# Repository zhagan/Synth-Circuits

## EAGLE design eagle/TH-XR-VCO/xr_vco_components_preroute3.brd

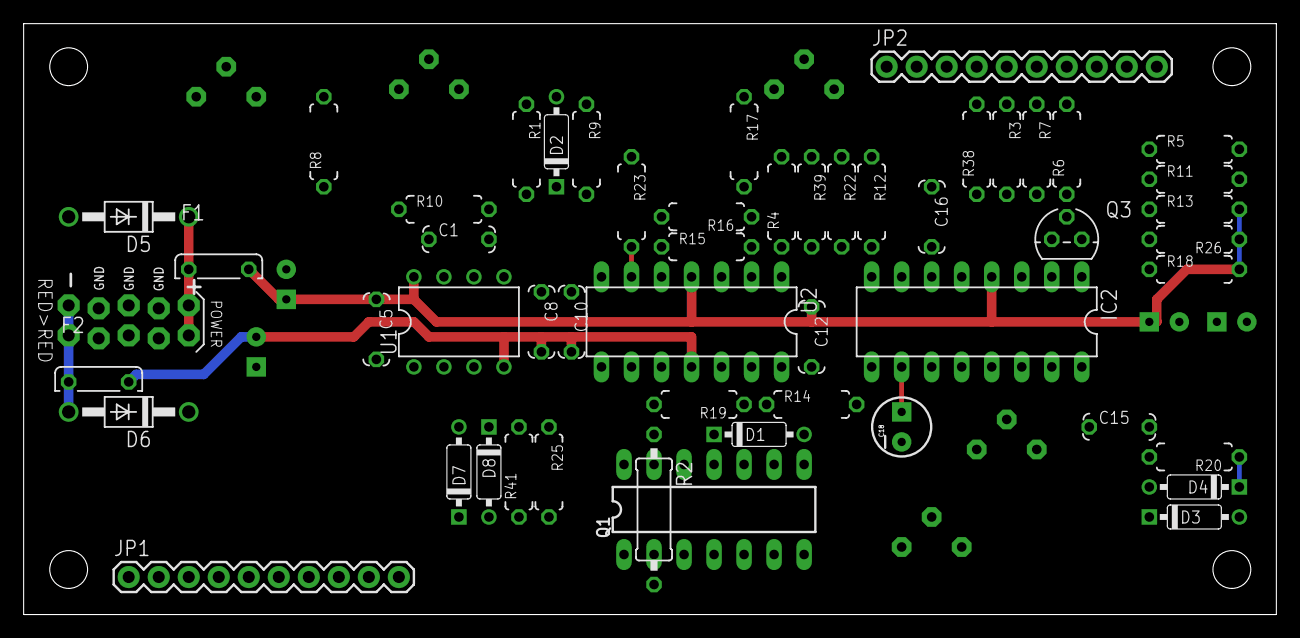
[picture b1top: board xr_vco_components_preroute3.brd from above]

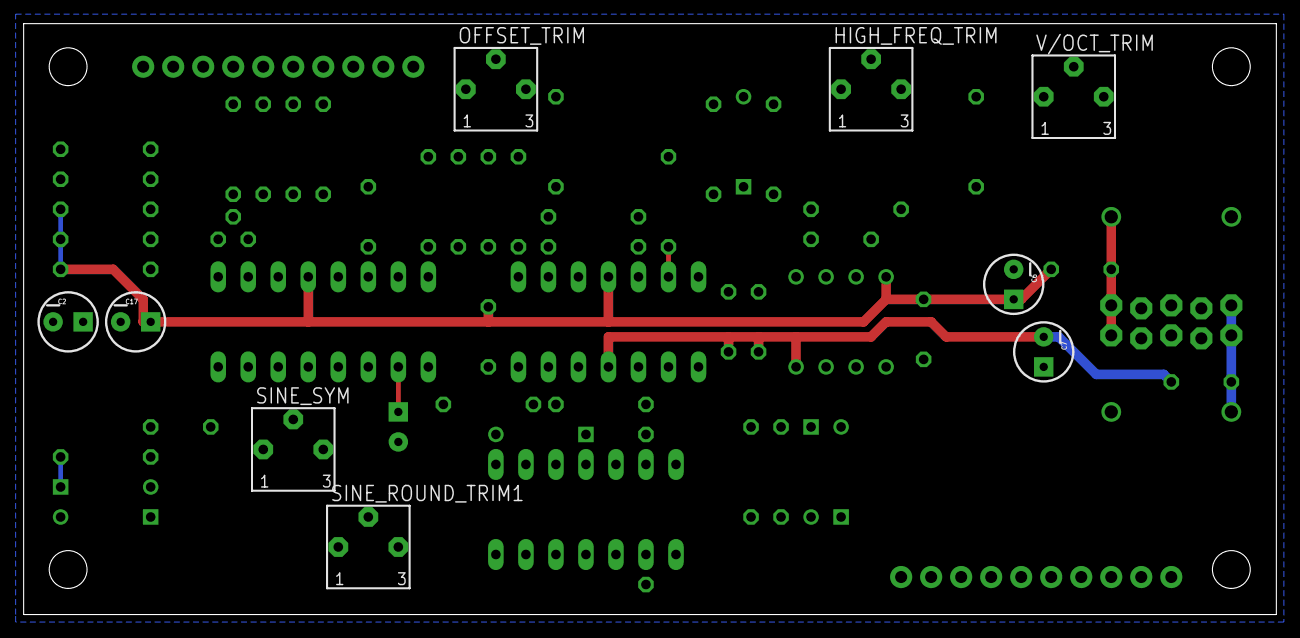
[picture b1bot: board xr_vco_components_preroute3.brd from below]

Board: 2 copper layers, 106.0 x 50.0 mm, 66 parts (9 on the bottom side), 48 nets.

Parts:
C1: 100pf; C050-024X044
C2, C6, C7: 10uf; CPOL-RADIAL-10UF-25V
C5, C8, C10, C12: 100n; C050-024X044
C15: 470pf; C050-024X044
C16: 0.047uf; C050-024X044
C17, C18: 4.7uf; CPOL-RADIAL-10UF-25V
D1, D2, D3, D4, D7, D8: 1N4148; DO35-7
D5, D6: 1N4001; DO41-10
F1, F2: FUSE; C050H075X075
HIGH_FREQ_TRIM: 1M; BOURNS_3362P_TRIMMER
IC2: DIL16
JP1, JP2: M10"; 1X10
OFFSET_TRIM: 50k; BOURNS_3362P_TRIMMER
Q1: THAT300P; DIL14
Q3: 2N3904; TO92D
R1: 47k; 7MM_RESISTOR
R2: 2k; 0309/12
R3: 82k; 7MM_RESISTOR
R4, R12: 1k; 7MM_RESISTOR
R5: 11k; 7MM_RESISTOR
R6: 20k; 7MM_RESISTOR
R7, R11: 5.6k; 7MM_RESISTOR
R8: 390R; 7MM_RESISTOR
R9, R13, R26: 4.7k; 7MM_RESISTOR
R10: 1.2m; 7MM_RESISTOR
R14, R18, R19, R23, R25: 10k; 7MM_RESISTOR
R15: 2.2M; 7MM_RESISTOR
R16: 3k; 7MM_RESISTOR
R17: 1.8k; 7MM_RESISTOR
R20: 100k; 7MM_RESISTOR
R22: 2.2k; 7MM_RESISTOR
R38: 150k; 7MM_RESISTOR
R39: 200k; 7MM_RESISTOR
R41: 220k; 7MM_RESISTOR
SINE_ROUND_TRIM1: 500 Ohm; BOURNS_3362P_TRIMMER
SINE_SYM: 25k; BOURNS_3362P_TRIMMER
SV1: EURO_POWER_HEADERLOCK_PADS; EURO_PWR_HEADER_LOCK
U1: LF442N; DIL08
U2: TL074P; DIL14
U$1, U$2, U$3, U$4: MOUNTING_HOLE
V/OCT_TRIM: 100R; BOURNS_3362P_TRIMMER

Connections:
+12V: C5.1, C6.1, C12.1, C17.1, F1.2, IC2.4, JP1.10, R7.2, R13.2, R18.2, R26.1, U1.8, U2.4
+12V_INLET: D5.C, F1.1, SV1.POS1, SV1.POS2
-12V: C7.2, C8.2, C10.2, F2.2, JP1.8, R10.1, R38.1, U1.4, U2.11
-12V_INLET: D6.A, F2.1, SV1.NEG1, SV1.NEG2
CATH_D4: D1.C, R19.1, U2.14
GND: C2.2, C5.2, C6.2, C7.1, C8.1, C10.1, C12.2, C17.2, C18.2, D3.A, D4.A, D5.A, D6.C, IC2.12, JP1.9, Q1.13, Q3.E, R8.1, R11.1, R12.1, R17.1, R23.1, SINE_SYM.2, SV1.GND1, SV1.GND2, SV1.GND3, SV1.GND4, SV1.GND5, SV1.GND6, U1.3, U1.5, U2.3, U2.10, U2.12
LIN_FM_CV: C1.2, JP1.4, Q1.3, R10.2, U1.6
unnamed: IC2.7, Q1.12
unnamed: D2.C, R1.2
unnamed: HIGH_FREQ_TRIM.1, R1.1
unnamed: IC2.2, R3.2
unnamed: R2.2, U1.1, V/OCT_TRIM.3
unnamed: OFFSET_TRIM.3, R3.1, R39.1, U2.2
unnamed: R8.2, V/OCT_TRIM.1
unnamed: D2.A, Q1.2, V/OCT_TRIM.2
unnamed: Q1.1, Q1.14, R9.2
unnamed: OFFSET_TRIM.1, R38.2
unnamed: R4.1, R39.2, U2.1
unnamed: C1.1, HIGH_FREQ_TRIM.3, R9.1, U1.7
unnamed: C2.1, R5.2, R6.2, R7.1, R11.2
unnamed: IC2.16, SINE_SYM.1
unnamed: IC2.13, SINE_ROUND_TRIM1.1
unnamed: IC2.15, SINE_SYM.3
unnamed: IC2.8, R12.2
unnamed: R18.1, R23.2, U2.6
unnamed: R15.1, R16.2, U2.7
unnamed: R19.2, R25.1, U2.13
unnamed: R15.2, R22.1, U2.5
unnamed: D1.A, D3.C, IC2.1, R14.1
unnamed: C15.2, R20.2
unnamed: D4.C, Q3.B, R20.1
unnamed: IC2.11, R13.1, R14.2, R22.2
unnamed: IC2.9, Q3.C, R26.2
unnamed: C16.2, IC2.6
unnamed: C16.1, IC2.5
unnamed: C18.1, IC2.10
unnamed: D7.A, D8.C, U2.8
unnamed: D8.A, R25.2, R41.1
PITCH_CV: JP1.7, R2.1, U1.2
SINE_TRI_OUT: JP1.3, R4.2
SKEW_IN: D7.C, JP1.5, R41.2, U2.9
SQR_OUT: JP1.2, R16.1, R17.2
SW_1: JP2.10, R6.1
SW_2: IC2.3, JP2.9
SW_3: JP2.8, R5.1
SW_4: JP2.7, SINE_ROUND_TRIM1.3
SW_5: IC2.14, JP2.6
SYNC_IN: C15.1, JP1.6

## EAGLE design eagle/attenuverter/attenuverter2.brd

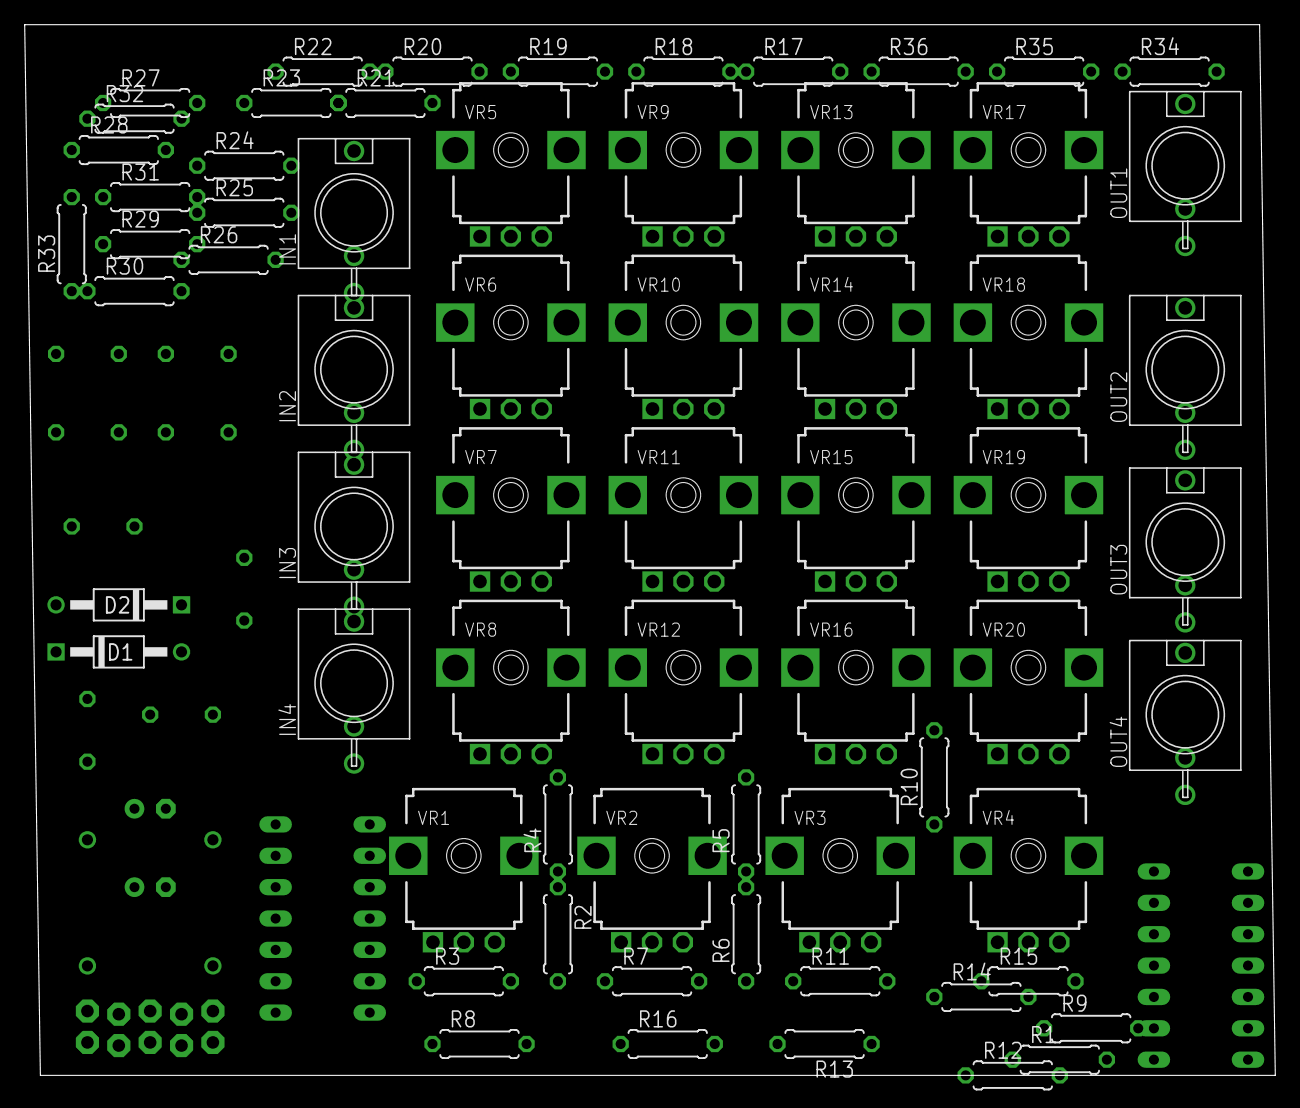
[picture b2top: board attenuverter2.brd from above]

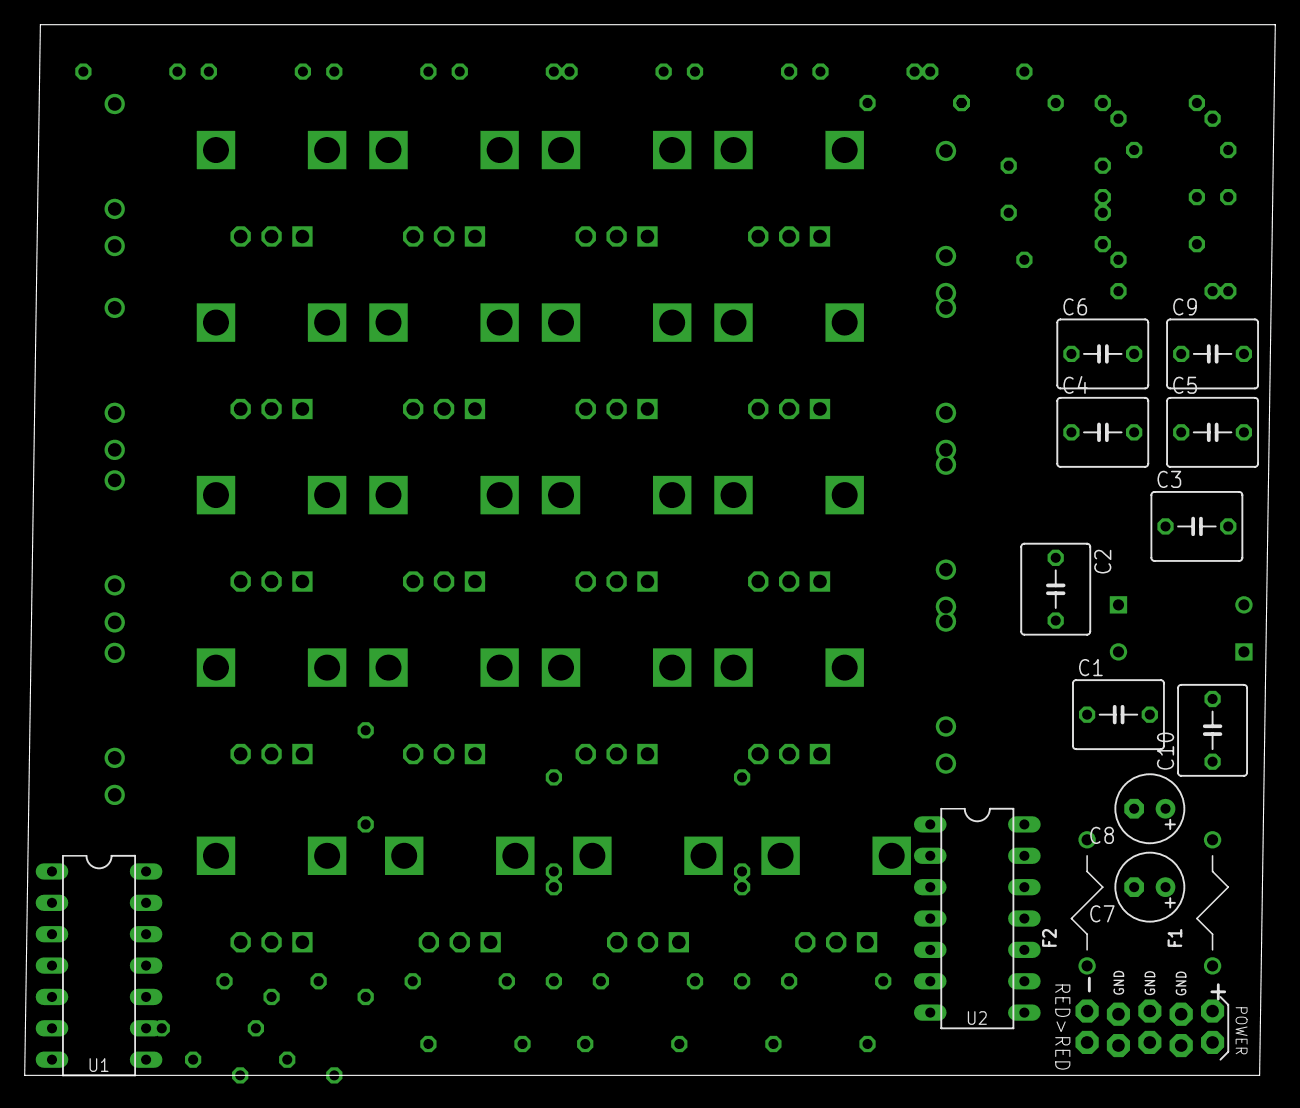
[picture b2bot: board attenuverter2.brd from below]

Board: 2 copper layers, 101.3 x 85.1 mm, 81 parts (15 on the bottom side), 49 nets, no tracks yet.

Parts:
C1, C2, C3, C4, C5, C6, C9, C10: 100nF; C050-055X075
C7, C8: 10uF; E2,5-6
D1, D2: 1N4007; DO41-4
F1, F2: MF-R500+; BOURNS-MF-R
IN1, IN2, IN3, IN4: THONKICONNNEW; WQP-PJ301M-12_JACK
OUT1, OUT2, OUT3, OUT4: THONKICONNNEW; WQP-PJ301M-12_JACK
R1, R2, R4, R5, R6, R8, R9, R10, R12, R13, R14, R16, R17, R18, R19, R20, R21, R22, R23, R24, R25, R26, R27, R28, R29, R30, R31, R32, R33, R34, R35, R36: 10k; 0207/7
R3, R7, R11, R15: 4.7k; 0207/7
SV1: EURO_POWER_HEADERLOCK_PADS; EURO_PWR_HEADER_LOCK
U1, U2: TL074_; DIL14
VR1, VR2, VR3, VR4, VR5, VR6, VR7, VR8, VR9, VR10, VR11, VR12, VR13, VR14, VR15, VR16, VR17, VR18, VR19, VR20: B10k; 9MM_SNAP-IN_POT

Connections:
+12V: C1.1, C3.1, C5.1, C7.+, C9.1, D1.C, F1.P$2, U1.4, U2.4
-12V: C2.2, C4.2, C6.2, C8.-, C10.2, D2.A, F2.P$1, U1.11, U2.11
GND: C1.2, C2.1, C3.2, C4.1, C5.2, C6.1, C7.-, C8.+, C9.2, C10.1, D1.A, D2.C, IN1.P$3_SLEEVE, IN2.P$3_SLEEVE, IN3.P$3_SLEEVE, IN4.P$3_SLEEVE, OUT1.P$3_SLEEVE, OUT2.P$3_SLEEVE, OUT3.P$3_SLEEVE, OUT4.P$3_SLEEVE, SV1.GND1, SV1.GND2, SV1.GND3, SV1.GND4, SV1.GND5, SV1.GND6, U2.3, U2.6, U2.9, U2.13, VR1.2, VR2.2, VR3.2, VR4.2, VR5.1, VR6.1, VR7.1, VR8.1, VR9.1, VR10.1, VR11.1, VR12.1, VR13.1, VR14.1, VR15.1, VR16.1, VR17.1, VR18.1, VR19.1, VR20.1
unnamed: R1.1, R2.2, R3.2, U1.3
unnamed: R2.1, R4.1, R19.2, U2.1
unnamed: R4.2, U1.2, VR1.3
unnamed: R3.1, VR1.1
unnamed: R22.2, R23.1, R24.2, R25.2, R26.2, U2.5
unnamed: R5.1, R6.2, R7.2, U1.5
unnamed: OUT1.P$1_TIP, R1.2, U1.1
unnamed: R8.2, U1.6, VR2.3
unnamed: F1.P$1, SV1.POS1, SV1.POS2
unnamed: F2.P$2, SV1.NEG1, SV1.NEG2
unnamed: R7.1, VR2.1
unnamed: OUT2.P$1_TIP, R5.2, U1.7
unnamed: R22.1, VR9.2
unnamed: R9.1, R10.2, R11.2, U1.10
unnamed: R12.2, U1.9, VR3.3
unnamed: R11.1, VR3.1
unnamed: OUT3.P$1_TIP, R9.2, U1.8
unnamed: IN4.P$1_TIP, VR8.3, VR12.3, VR16.3, VR20.3
unnamed: R13.1, R14.2, R15.2, U1.12
unnamed: R16.2, U1.13, VR4.3
unnamed: R15.1, VR4.1
unnamed: OUT4.P$1_TIP, R13.2, U1.14
unnamed: IN2.P$1_TIP, VR6.3, VR10.3, VR14.3, VR18.3
unnamed: R17.2, R18.2, R19.1, R20.2, R21.2, U2.2
unnamed: R18.1, VR5.2
unnamed: R17.1, VR6.2
unnamed: IN3.P$1_TIP, VR7.3, VR11.3, VR15.3, VR19.3
unnamed: R20.1, VR7.2
unnamed: R21.1, VR8.2
unnamed: R24.1, VR10.2
unnamed: R25.1, VR11.2
unnamed: R26.1, VR12.2
unnamed: IN1.P$1_TIP, VR5.3, VR9.3, VR13.3, VR17.3
unnamed: R6.1, R8.1, R23.2, U2.7
unnamed: R27.2, R28.1, R29.2, R30.2, R31.2, U2.10
unnamed: R27.1, VR13.2
unnamed: R29.1, VR14.2
unnamed: R30.1, VR15.2
unnamed: R31.1, VR16.2
unnamed: R10.1, R12.1, R28.2, U2.8
unnamed: R32.2, R33.1, R34.2, R35.2, R36.2, U2.12
unnamed: R32.1, VR17.2
unnamed: R34.1, VR18.2
unnamed: R35.1, VR19.2
unnamed: R36.1, VR20.2
unnamed: R14.1, R16.1, R33.2, U2.14

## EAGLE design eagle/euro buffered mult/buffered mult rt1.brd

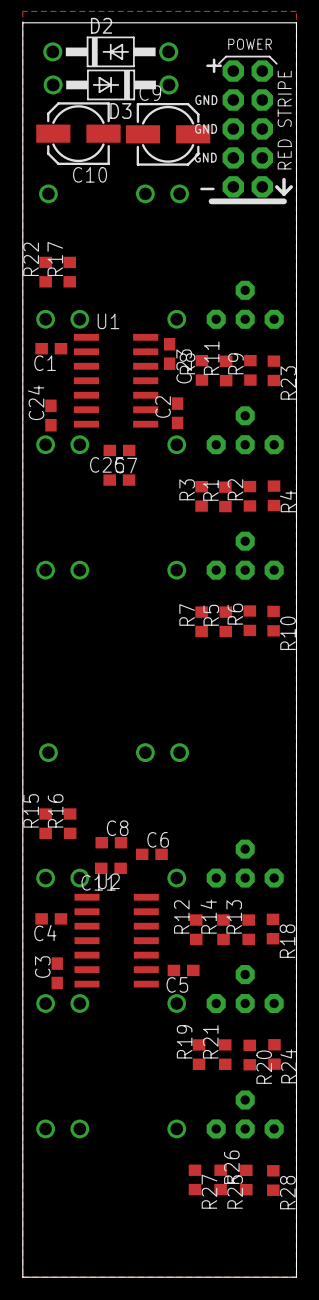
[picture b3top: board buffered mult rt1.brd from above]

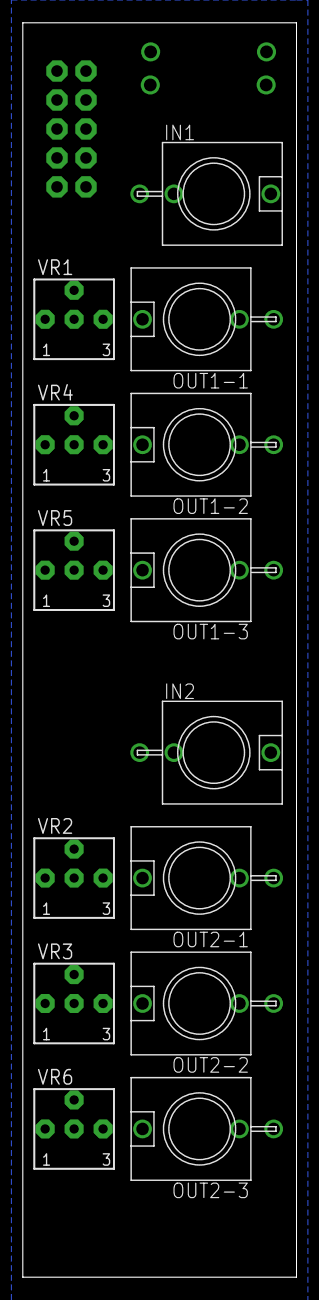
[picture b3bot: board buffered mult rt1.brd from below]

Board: 2 copper layers, 24.0 x 110.0 mm, 61 parts (14 on the bottom side), 38 nets, no tracks yet.

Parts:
C1, C4: 6pf; C0603
C2, C3, C5, C6, C23, C24: 10pf; C0603
C7, C8, C11, C25: 0.1uf; C0603
C9, C10: 10uf; 153CLV-0505
D2, D3: 1N4004; DO41-10
IN1, IN2: THONKICONNNEW; WQP-PJ301M-12_JACK
OUT1-1, OUT1-2, OUT1-3, OUT2-1, OUT2-2, OUT2-3: THONKICONNNEW; WQP-PJ301M-12_JACK
R1, R2, R5, R6, R8, R9, R12, R13, R19, R20, R25, R26: 49.9k; R0603
R3, R7, R11, R14, R21, R27: 301R; R0603
R4, R10, R18, R23, R24, R28: 13.3k; R0603
R15, R22: 100k; R0603
R16, R17: 107k; R0603
SV1: EURO_POWER_HEADERFAT_PADS; EURO_PWR_HEADER_FAT
U1, U2: TL074_SMD; SO14
VR1, VR2, VR3, VR4, VR5, VR6: 2k; BOURNS_3362P_TRIMMER

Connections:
GND: C7.1, C8.2, C9.-, C10.+, C11.1, C25.2, D2.A, D3.C, IN1.P$3_SLEEVE, IN2.P$3_SLEEVE, OUT1-1.P$3_SLEEVE, OUT1-2.P$3_SLEEVE, OUT1-3.P$3_SLEEVE, OUT2-1.P$3_SLEEVE, OUT2-2.P$3_SLEEVE, OUT2-3.P$3_SLEEVE, R4.2, R10.2, R18.2, R23.2, R24.2, R28.2, SV1.3, SV1.4, SV1.5, SV1.6, SV1.7, SV1.8, U1.3, U1.5, U1.10, U1.12, U2.3, U2.5, U2.10, U2.12
unnamed: IN1.P$1_TIP, R22.2
unnamed: C4.1, R16.2, U2.1, VR2.3, VR3.3, VR6.3
unnamed: C1.2, R17.1, R22.1, U1.2
unnamed: C4.2, R15.1, R16.1, U2.2
unnamed: R18.1, VR2.1
unnamed: R23.1, VR1.1
unnamed: C1.1, R17.2, U1.1, VR1.3, VR4.3, VR5.3
unnamed: R13.2, VR2.2, VR2.4
unnamed: R9.2, VR1.2, VR1.4
unnamed: C24.2, R8.1, R9.1, U1.6
unnamed: C3.2, R12.1, R13.1, U2.6
unnamed: C24.1, R11.1, U1.7
unnamed: OUT1-1.P$1_TIP, R8.2, R11.2
unnamed: C3.1, R14.1, U2.7
unnamed: R4.1, VR4.1
unnamed: OUT2-1.P$1_TIP, R12.2, R14.2
unnamed: R24.1, VR3.1
unnamed: R20.2, VR3.2, VR3.4
unnamed: R2.2, VR4.2, VR4.4
unnamed: C2.2, R1.1, R2.1, U1.9
unnamed: C2.1, R3.1, U1.8
unnamed: C5.2, R19.1, R20.1, U2.9
unnamed: C5.1, R21.1, U2.8
unnamed: OUT1-2.P$1_TIP, R1.2, R3.2
unnamed: OUT2-2.P$1_TIP, R19.2, R21.2
unnamed: R28.1, VR6.1
unnamed: R26.2, VR6.2, VR6.4
unnamed: C6.2, R25.1, R26.1, U2.13
unnamed: C6.1, R27.1, U2.14
unnamed: OUT2-3.P$1_TIP, R25.2, R27.2
unnamed: R10.1, VR5.1
unnamed: R6.2, VR5.2, VR5.4
unnamed: C23.2, R5.1, R6.1, U1.13
PWR+12V: C8.1, C9.+, C25.1, D2.C, SV1.9, SV1.10, U1.4, U2.4
PWR-12V: C7.2, C10.-, C11.2, D3.A, SV1.1, SV1.2, U1.11, U2.11
TO-IN2: C23.1, IN2.P$2_SWITCH, OUT1-3.P$1_TIP, R5.2, R7.1, R7.2, U1.14
TO-IN3: IN2.P$1_TIP, R15.2

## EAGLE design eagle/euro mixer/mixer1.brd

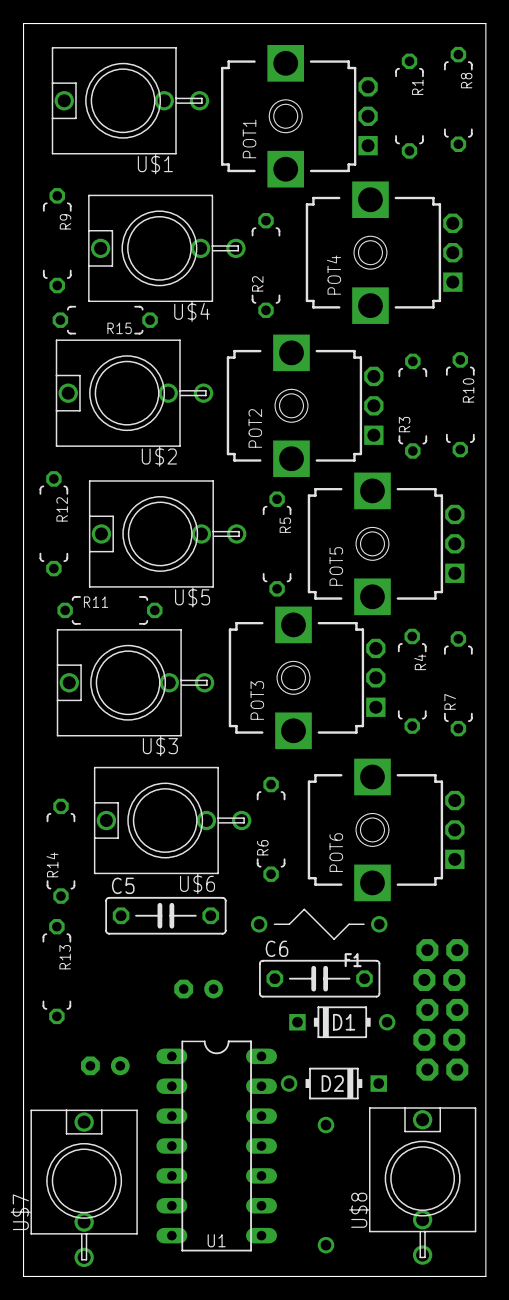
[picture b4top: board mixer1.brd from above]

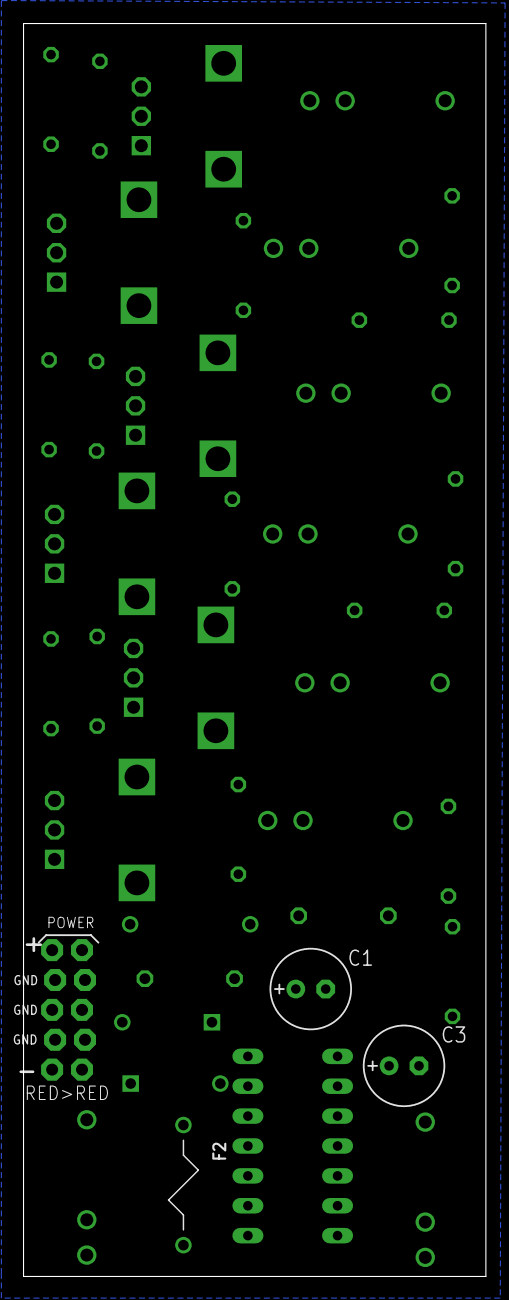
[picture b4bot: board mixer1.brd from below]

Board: 2 copper layers, 39.3 x 106.5 mm, 39 parts (4 on the bottom side), 32 nets, no tracks yet.

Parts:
C1, C3: 10uF; E2,5-7
C5, C6: 100nF; C075-032X103
D1, D2: 1N4007; DO41-3
F1, F2: MF-R500+; BOURNS-MF-R
POT1, POT2, POT3, POT4, POT5, POT6: A100K; 9MM_SNAP-IN_POT
R1, R2, R3, R4, R5, R6, R7, R8, R9, R10, R13, R14, R15: 100K; 7MM_RESISTOR
R11, R12: 1K; 7MM_RESISTOR
SV1: EURO_POWER_HEADERLOCK_PADS; EURO_PWR_HEADER_LOCK
U1: TL074_; DIL14
U$1, U$2, U$3, U$4, U$5, U$6, U$7, U$8: THONKICONNNEW; WQP-PJ301M-12_JACK

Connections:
+12V: C1.+, C6.1, D1.C, F1.P$2, U1.4
-12V: C3.-, C5.2, D2.A, F2.P$2, U1.11
GND: C1.-, C3.+, C5.1, C6.2, D1.A, D2.C, POT1.1, POT2.1, POT3.1, POT4.1, POT5.1, POT6.1, SV1.GND1, SV1.GND2, SV1.GND3, SV1.GND4, SV1.GND5, SV1.GND6, U$1.P$3_SLEEVE, U$2.P$3_SLEEVE, U$3.P$3_SLEEVE, U$4.P$3_SLEEVE, U$5.P$3_SLEEVE, U$6.P$3_SLEEVE, U$7.P$3_SLEEVE, U$8.P$3_SLEEVE
unnamed: POT2.3, U$2.P$1_TIP
unnamed: POT2.2, R2.1
unnamed: POT1.3, U$1.P$1_TIP
unnamed: POT1.2, R1.1
unnamed: POT3.3, U$3.P$1_TIP
unnamed: POT3.2, R3.1
unnamed: POT4.3, U$4.P$1_TIP
unnamed: POT4.2, R4.1
unnamed: POT5.3, U$5.P$1_TIP
unnamed: POT5.2, R5.1
unnamed: POT6.3, U$6.P$1_TIP
unnamed: POT6.2, R6.1
unnamed: R1.2, R2.2, R3.2, U1.2
unnamed: R7.1, U1.3
unnamed: R7.2, R9.1, U1.1
unnamed: R9.2, U1.9
unnamed: R14.1, U1.10
unnamed: R11.2, U$7.P$1_TIP
unnamed: R8.2, R10.1, U1.7
unnamed: R8.1, U1.5
unnamed: R15.1, U1.12
unnamed: R12.1, R15.2, U1.14
unnamed: R10.2, U1.13
unnamed: R4.2, R5.2, R6.2, R13.1, U1.6
unnamed: R11.1, R14.2, U1.8
unnamed: R13.2, U$7.P$2_SWITCH
unnamed: R12.2, U$8.P$1_TIP
unnamed: F2.P$1, SV1.NEG1, SV1.NEG2
unnamed: F1.P$1, SV1.POS1, SV1.POS2

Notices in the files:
parts and their libraries:
SparkFun-Passives: Licensing: CC v3.0 Share-Alike You are welcome to use this library for commercial purposes.
that-corp: Copyright (C) 2008-2010, Bob Starr
